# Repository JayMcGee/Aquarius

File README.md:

# Aquarius

The aquarius water quality evaluation station will be a programmable autonomous terminal. It will have acces to cellular network to transmit data to CloudIA, a scientific database and data visualisation interface.

The terminal evaluates water quality by acquiring acidity level (pH), water conductivity (µS/cm), dissolved oxygen (mg/L) and temperature(℃).  

-------------------------------------------------------------------------------------------------------------------------

La station d’évaluation de la qualité de l’eau Aquarius sera une borne autonome programmable. Elle aura la capacité de communiquer par réseau cellulaire ses données au logiciel CloudIA, une interface de visualisation de données scientifiques .

La borne permettra d’évaluer la qualité de l’eau en recueillant des mesures d’acidité (pH), de conductivité (µS/cm), de la concentration d’oxygène dissous (mg/L) et de la température (℃).

-------------------------------------------------------------------------------------------------------------------------

Aquarius is a Beaglebone Black with pH, dissolved oxygen, and conductivity sensors built by Atlas Scientific and a water temperature sensor by Dallas Semiconductor.

Each sensor has its own driver to calibrate or read a value. Those drivers are executed by an interface hosted on the apache server (/var/www) with a real-time interface written in Html connected to the server with Node.Js.

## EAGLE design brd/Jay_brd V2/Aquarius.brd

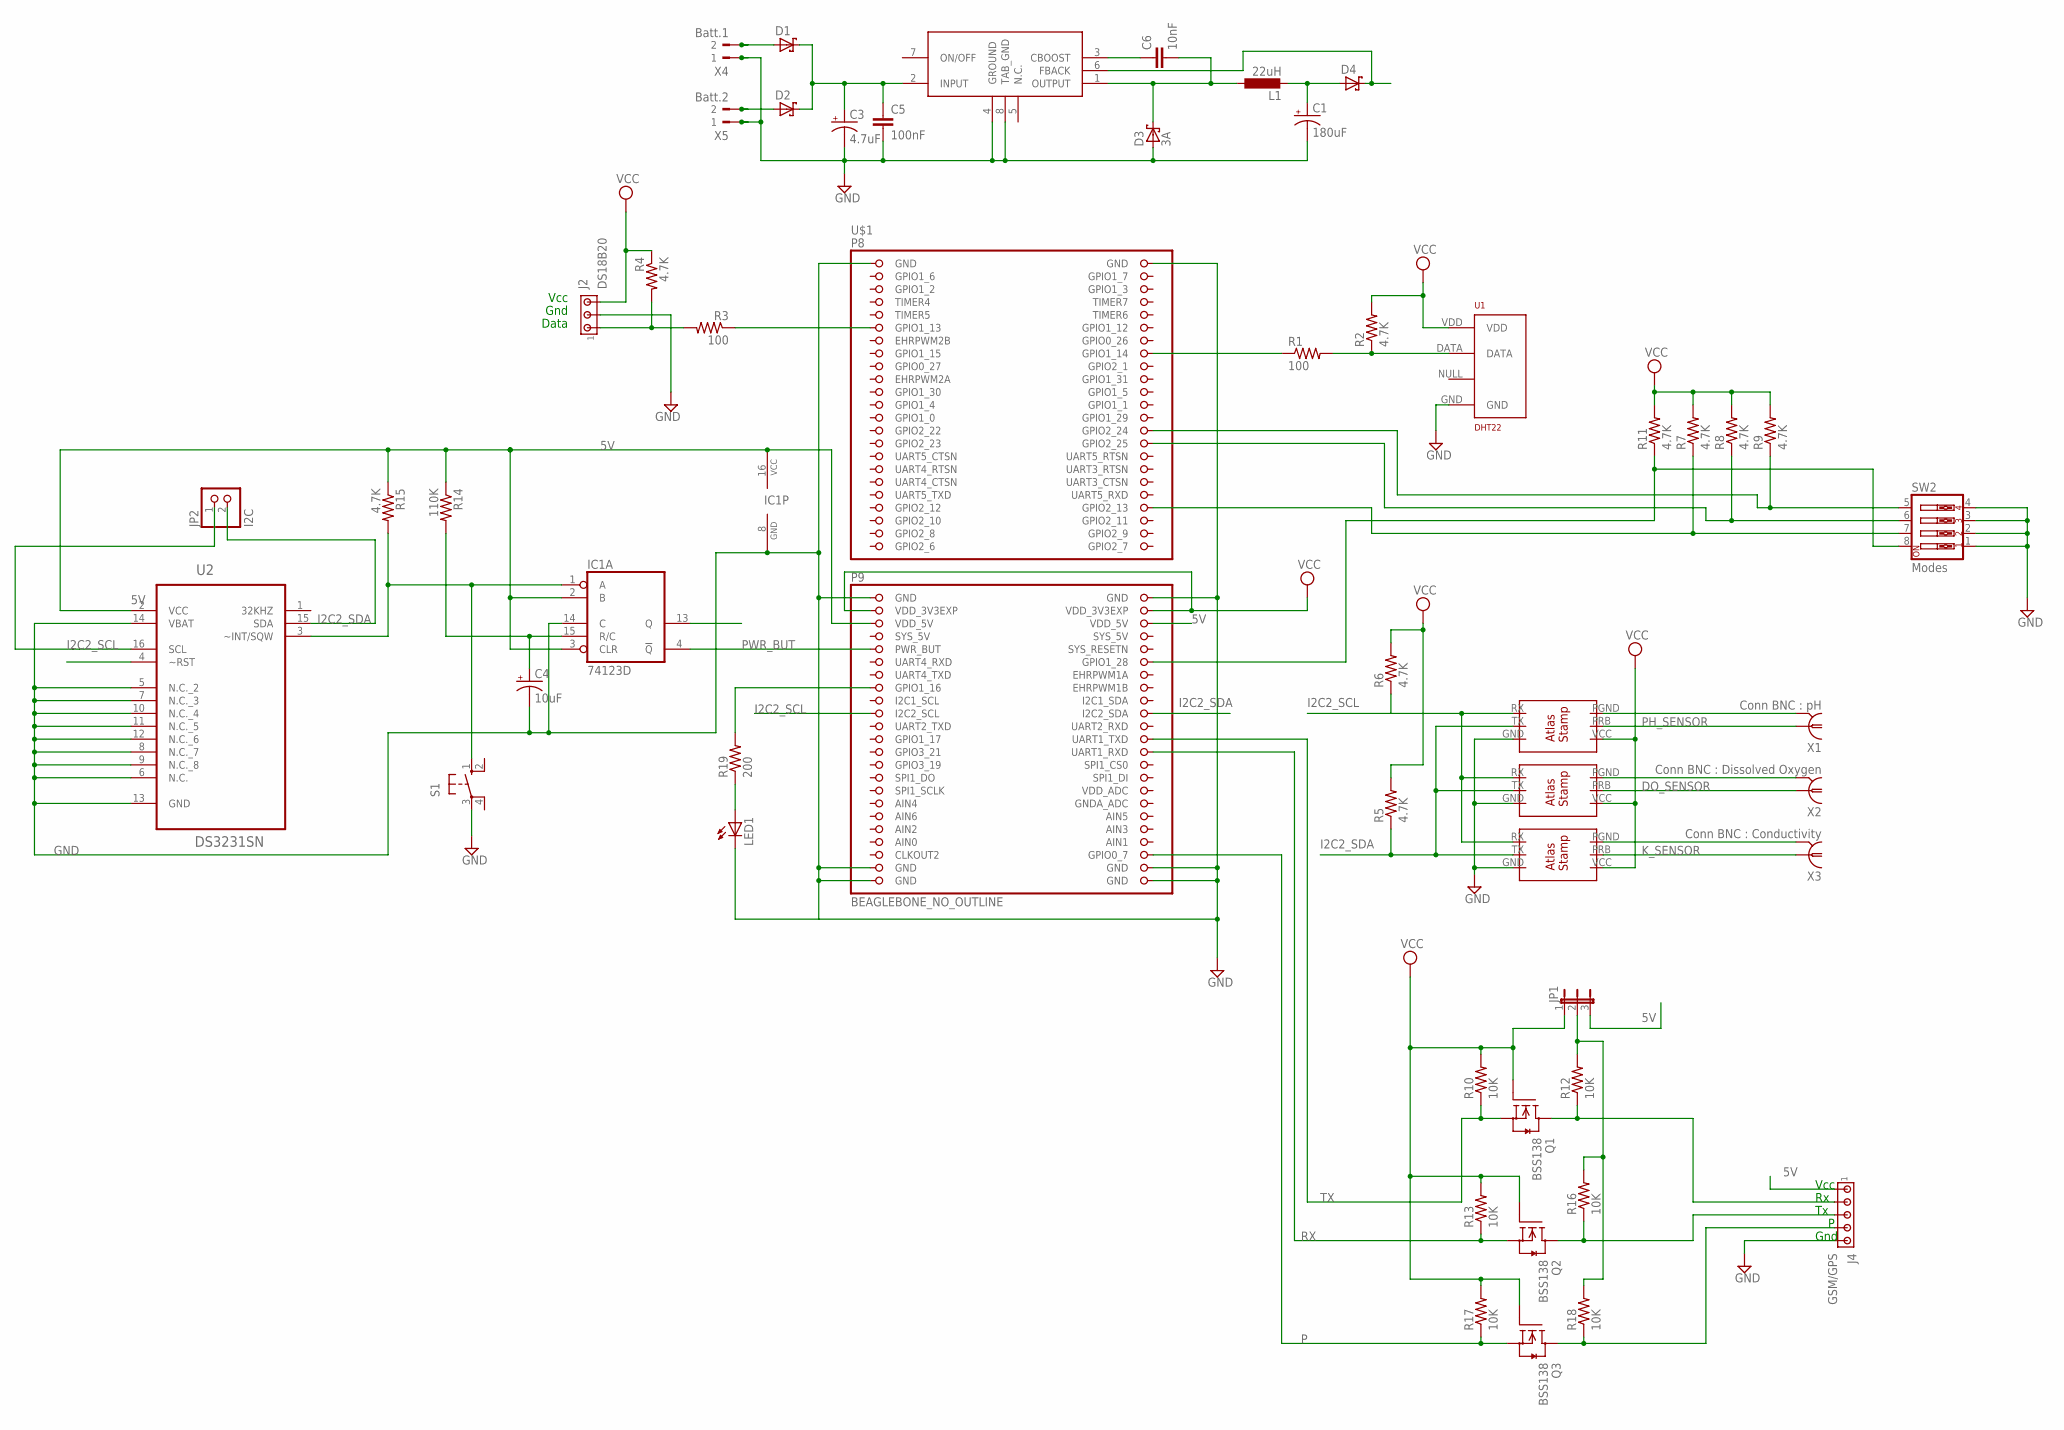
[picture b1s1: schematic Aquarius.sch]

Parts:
C1: 180uF; PANASONIC_D
C3: 4.7uF; PANASONIC_B
C4: 10uF; PANASONIC_B
C5: 100nF; C0805
C6: 10nF; C0805
D1, D2, D4: SCHOTTKY-DIODEDO201T15; DO201T15
D3: 3A; DO201T15
IC1: 74123D; SO16
J2: DS18B20; 10X03MTA
J4: GSM/GPS; 10X05MTA
JP1: JP2E; JP2
JP2: I2C; 1X02
L1: 22uH; EPCOS-10X10
LED1: LEDCHIP-LED0805; CHIP-LED0805
LM2678: LM2678KTW0007B; TO-PMOD7
Q1, Q2, Q3: BSS138; SOT23
R1, R3: 100; R0805
R2, R4, R5, R6, R7, R8, R9, R11, R15: 4.7K; R0805
R10, R12, R13, R16, R17, R18: 10K; R0805
R14: 110K; R0805
R19: 200; R0805
S1: 10-XX; B3F-10XX
SW2: Modes; EDG-04
U1: DHT22; AM2302
U2: DS3231SN; SOIC127P1032X265-16N
U$1: BEAGLEBONE_NO_OUTLINE; BEAGLEBONE_SHIELD_NO_OUTLINE
U$2, U$3, U$4: ATLAS_STAMP
X1: Conn BNC : pH; AMP_227161
X2: Conn BNC : Dissolved Oxygen; AMP_227161
X3: Conn BNC : Conductivity; AMP_227161
X4: Batt.1; 180G-2
X5: Batt.2; 180G-2

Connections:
5V: D4.C, IC1.2 (B), IC1.3 (CLR), IC1.16 (VCC), J4.1, JP1.3, LM2678.6 (FBACK), R14.1, R15.1, U2.2 (VCC), U$1.51 (VDD_5V), U$1.52 (VDD_5V)
AIN0: U$1.85 (AIN0)
DO_SENSOR: U$3.PRB, X2.1
GND: C1.-, C3.-, C4.-, C5.2, D3.A, IC1.8 (GND), IC1.14 (C), J2.2, J4.5, LED1.C, LM2678.4 (GROUND), LM2678.8 (TAB_GND), S1.3, SW2.1, SW2.2, SW2.3, SW2.4, U1.GND, U2.5 (N.C._2), U2.6 (N.C.), U2.7 (N.C._3), U2.8 (N.C._7), U2.9 (N.C._8), U2.10 (N.C._4), U2.11 (N.C._5), U2.12 (N.C._6), U2.13 (GND), U2.14 (VBAT), U$1.1 (GND), U$1.2 (GND), U$1.47 (GND), U$1.48 (GND), U$1.89 (GND), U$1.90 (GND), U$1.91 (GND), U$1.92 (GND), U$2.GND, U$3.GND, U$4.GND, X4.1, X5.1
I2C2_SCL: JP2.1, R6.1, U2.16 (SCL), U$1.65 (I2C2_SCL), U$2.RX, U$3.RX, U$4.RX
I2C2_SDA: JP2.2, R5.1, U2.15 (SDA), U$2.TX, U$3.TX, U$4.TX
INT: IC1.1 (A), R15.2, S1.1 (S), U2.3 (~INT/SQW)
K_SENSOR: U$4.PRB, X3.1
unnamed: J4.4, Q3.3 (D), R18.1
unnamed: D1.A, X4.2
unnamed: R1.2, R2.1, U1.DATA
unnamed: R3.1, U$1.11 (GPIO1_13)
unnamed: J2.1, R3.2, R4.2
unnamed: R1.1, U$1.16 (GPIO1_14)
unnamed: R7.1, SW2.7, U$1.40 (GPIO2_13)
unnamed: D2.A, X5.2
unnamed: C6.1, LM2678.3 (CBOOST)
unnamed: C3.+, C5.1, D1.C, D2.C, LM2678.2 (INPUT)
unnamed: U$2.PGND, X1.2
unnamed: C6.2, D3.C, L1.P$1 (1), LM2678.1 (OUTPUT)
unnamed: U$4.PGND, X3.2
unnamed: U$3.PGND, X2.2
unnamed: C1.+, D4.A, L1.P$2 (2)
unnamed: C4.+, IC1.15 (R/C), R14.2
unnamed: R11.1, SW2.8, U$1.58 (GPIO1_28)
unnamed: R8.1, SW2.6, U$1.30 (GPIO2_25)
unnamed: R9.1, SW2.5, U$1.28 (GPIO2_24)
unnamed: J4.3, Q2.3 (D), R16.1
unnamed: J4.2, Q1.3 (D), R12.1
unnamed: JP1.2, R12.2, R16.2, R18.2
unnamed: LED1.A, R19.1
unnamed: R19.2, U$1.61 (GPIO1_16)
P: Q3.2 (S), R17.1, U$1.88 (GPIO0_7)
PH_SENSOR: U$2.PRB, X1.1
PWR_BUT: IC1.4 (!Q), U$1.55 (PWR_BUT)
RX: Q2.2 (S), R13.1, U$1.72 (UART1_RXD)
SYS_5V: U$1.53 (SYS_5V)
TX: Q1.2 (S), R10.1, U$1.70 (UART1_TXD)
VCC: J2.3, JP1.1, Q1.1 (G), Q2.1 (G), Q3.1 (G), R2.2, R4.1, R5.2, R6.2, R7.2, R8.2, R9.2, R10.2, R11.2, R13.2, R17.2, U1.VDD, U$1.49 (VDD_3V3EXP), U$1.50 (VDD_3V3EXP), U$2.VCC, U$3.VCC, U$4.VCC

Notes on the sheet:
Vcc
Gnd
Data

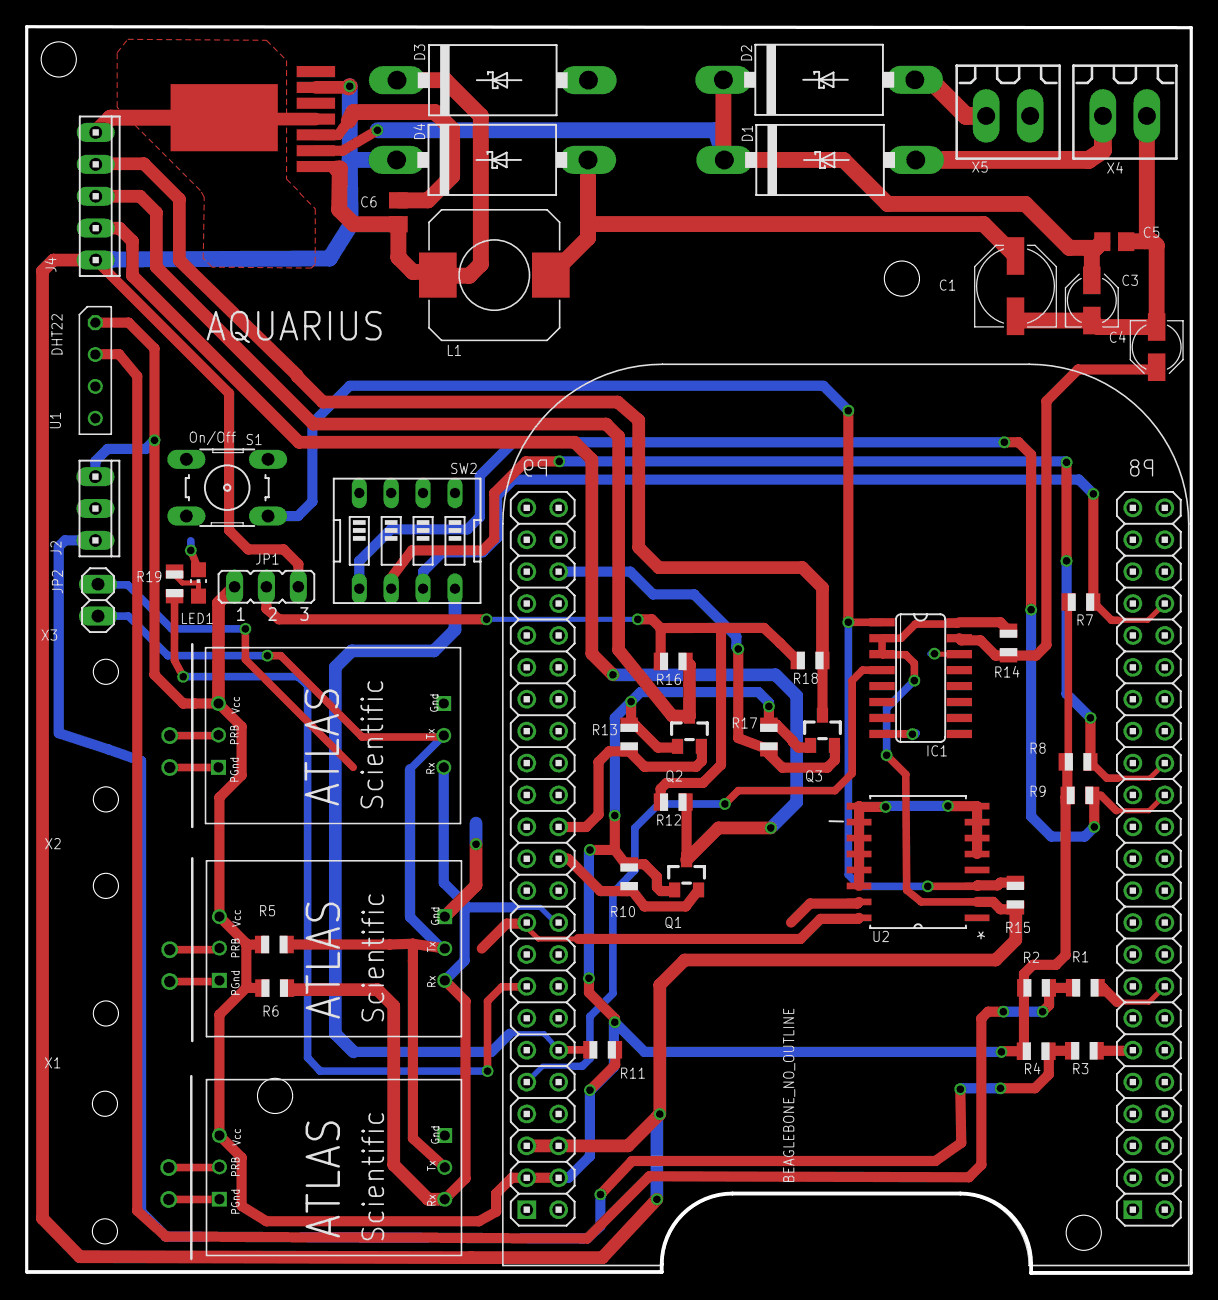
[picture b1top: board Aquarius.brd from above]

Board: 2 copper layers, 92.7 x 99.2 mm, 53 parts (1 on the bottom side), 37 nets.

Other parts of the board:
DRILEGEND: DRILEGEND

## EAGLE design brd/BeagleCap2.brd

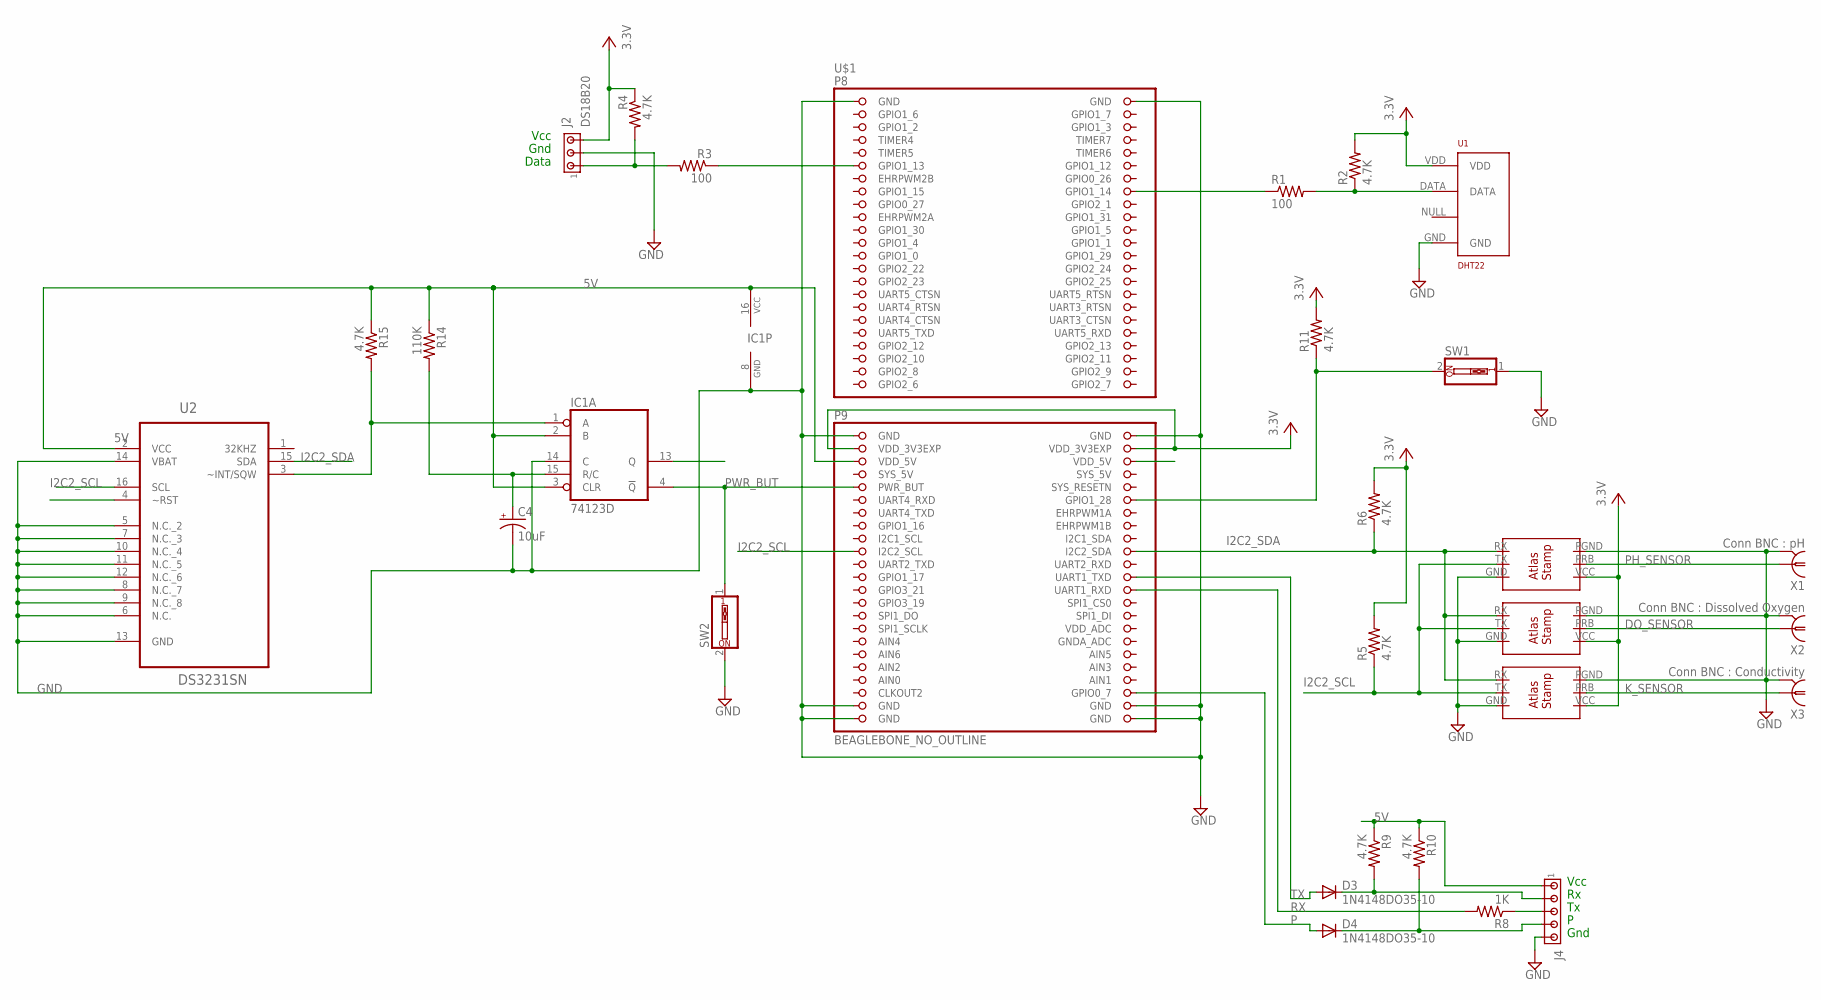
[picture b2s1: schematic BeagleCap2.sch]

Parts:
C4: 10uF; E2-5
D3, D4: 1N4148DO35-10; DO35-10
IC1: 74123D; SO16
J2: DS18B20; 10X03MTA
J4: MTA05-100; 10X05MTA
R1, R3: 100; R0805
R2, R4, R5, R6, R9, R10, R11, R15: 4.7K; R0805
R8: 1K; R0805
R14: 110K; R0805
SW1, SW2: SW_DIP-1; EDG-01
U1: DHT22; AM2302
U2: DS3231SN; SOIC127P1032X265-16N
U$1: BEAGLEBONE_NO_OUTLINE; BEAGLEBONE_SHIELD_NO_OUTLINE
U$2, U$3, U$4: ATLAS_STAMP
X1: Conn BNC : pH; AMP_227161
X2: Conn BNC : Dissolved Oxygen; AMP_227161
X3: Conn BNC : Conductivity; AMP_227161

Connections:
3.3V: J2.3, R2.2, R4.1, R5.2, R6.2, U1.VDD, U$1.49 (VDD_3V3EXP), U$1.50 (VDD_3V3EXP), U$2.VCC, U$3.VCC, U$4.VCC
5V: IC1.2 (B), IC1.3 (CLR), IC1.16 (VCC), J4.1, R9.1, R10.1, R14.1, R15.1, U2.2 (VCC), U$1.51 (VDD_5V)
AIN0: U$1.85 (AIN0)
DO_SENSOR: U$3.PRB, X2.1
GND: C4.-, IC1.8 (GND), IC1.14 (C), J2.2, J4.5, SW1.1, SW2.2, U1.GND, U2.5 (N.C._2), U2.6 (N.C.), U2.7 (N.C._3), U2.8 (N.C._7), U2.9 (N.C._8), U2.10 (N.C._4), U2.11 (N.C._5), U2.12 (N.C._6), U2.13 (GND), U2.14 (VBAT), U$1.1 (GND), U$1.2 (GND), U$1.47 (GND), U$1.48 (GND), U$1.89 (GND), U$1.90 (GND), U$1.91 (GND), U$1.92 (GND), U$2.GND, U$2.PGND, U$3.GND, U$3.PGND, U$4.GND, U$4.PGND, X1.2, X2.2, X3.2
I2C2_SCL: R5.1, U2.16 (SCL), U$1.65 (I2C2_SCL), U$2.TX, U$3.TX, U$4.TX
I2C2_SDA: R6.1, U2.15 (SDA), U$1.66 (I2C2_SDA), U$2.RX, U$3.RX, U$4.RX
INT: IC1.1 (A), R15.2, U2.3 (~INT/SQW)
K_SENSOR: U$4.PRB, X3.1
unnamed: R1.2, R2.1, U1.DATA
unnamed: R3.1, U$1.11 (GPIO1_13)
unnamed: J2.1, R3.2, R4.2
unnamed: R1.1, U$1.16 (GPIO1_14)
unnamed: R11.1, SW1.2, U$1.58 (GPIO1_28)
unnamed: D3.C, J4.2, R9.2
unnamed: J4.3, R8.1
unnamed: D4.C, J4.4, R10.2
unnamed: C4.+, IC1.15 (R/C), R14.2
P: D4.A, U$1.88 (GPIO0_7)
PH_SENSOR: U$2.PRB, X1.1
PWR_BUT: IC1.4 (!Q), SW2.1, U$1.55 (PWR_BUT)
RX: R8.2, U$1.72 (UART1_RXD)
SYS_5V: U$1.53 (SYS_5V)
TX: D3.A, U$1.70 (UART1_TXD)
VCC: R11.2

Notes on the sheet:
Vcc
Gnd
Data

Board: 2 copper layers, 29 parts (1 on the bottom side), 22 nets, no tracks yet.

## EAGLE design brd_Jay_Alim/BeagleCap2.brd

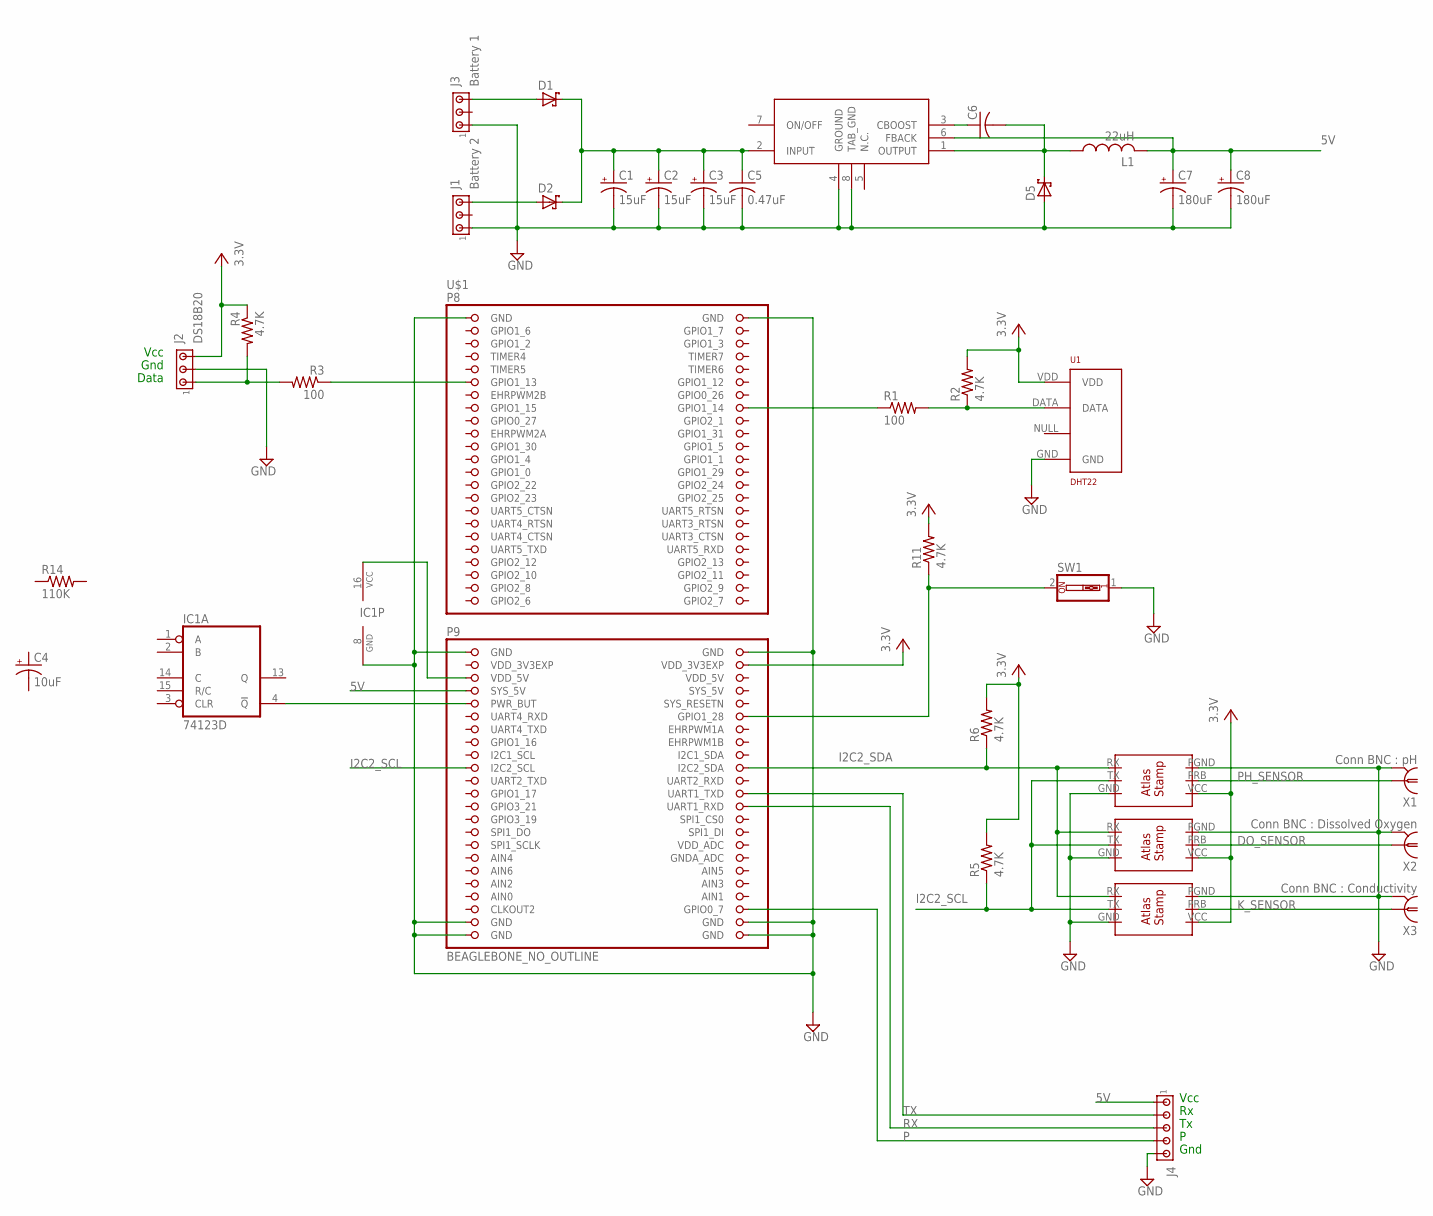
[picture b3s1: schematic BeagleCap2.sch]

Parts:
C1, C2, C3: 15uF; 153CLV-0405
C4: 10uF; E2-5
C5: 0.47uF; C025-025X050
C6: C-US025-025X050; C025-025X050
C7, C8: 180uF; E2,5-7
D1, D2: SCHOTTKY-DIODECB417-15; CB417-15
D5: SCHOTTKY-DIODEDO41-7; DO41-7
IC1: 74123D; SO16
J1: Battery 2; 10X03MTA
J2: DS18B20; 10X03MTA
J3: Battery 1; 10X03MTA
J4: MTA05-100; 10X05MTA
L1: 22uH; 0204/7
R1, R3: 100; R0805
R2, R4, R5, R6, R11: 4.7K; R0805
R14: 110K; R0805
SW1: SW_DIP-1; EDG-01
U1: DHT22; AM2302
U$1: BEAGLEBONE_NO_OUTLINE; BEAGLEBONE_SHIELD_NO_OUTLINE
U$2, U$3, U$4: ATLAS_STAMP
U$7: LM2678KTW0007B; TO-PMOD7
X1: Conn BNC : pH; AMP_227161
X2: Conn BNC : Dissolved Oxygen; AMP_227161
X3: Conn BNC : Conductivity; AMP_227161

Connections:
3.3V: J2.3, R2.2, R4.1, R5.2, R6.2, U1.VDD, U$1.50 (VDD_3V3EXP), U$2.VCC, U$3.VCC, U$4.VCC
5V: C7.+, C8.+, IC1.16 (VCC), J4.1, L1.2, U$1.51 (VDD_5V), U$1.53 (SYS_5V), U$7.6 (FBACK)
AIN0: U$1.85 (AIN0)
DO_SENSOR: U$3.PRB, X2.1
GND: C1.-, C2.-, C3.-, C5.2, C7.-, C8.-, D5.A, IC1.8 (GND), J1.1, J2.2, J3.1, J4.5, SW1.1, U1.GND, U$1.1 (GND), U$1.2 (GND), U$1.47 (GND), U$1.48 (GND), U$1.89 (GND), U$1.90 (GND), U$1.91 (GND), U$1.92 (GND), U$2.GND, U$2.PGND, U$3.GND, U$3.PGND, U$4.GND, U$4.PGND, U$7.4 (GROUND), U$7.8 (TAB_GND), X1.2, X2.2, X3.2
I2C2_SCL: R5.1, U$1.65 (I2C2_SCL), U$2.TX, U$3.TX, U$4.TX
I2C2_SDA: R6.1, U$1.66 (I2C2_SDA), U$2.RX, U$3.RX, U$4.RX
K_SENSOR: U$4.PRB, X3.1
unnamed: D2.A, J1.3
unnamed: D1.A, J3.3
unnamed: R1.2, R2.1, U1.DATA
unnamed: R3.1, U$1.11 (GPIO1_13)
unnamed: J2.1, R3.2, R4.2
unnamed: R1.1, U$1.16 (GPIO1_14)
unnamed: R11.1, SW1.2, U$1.58 (GPIO1_28)
unnamed: C1.+, C2.+, C3.+, C5.1, D1.C, D2.C, U$7.2 (INPUT)
unnamed: C6.1, U$7.3 (CBOOST)
unnamed: C6.2, D5.C, L1.1, U$7.1 (OUTPUT)
unnamed: IC1.4 (!Q), U$1.55 (PWR_BUT)
P: J4.4, U$1.88 (GPIO0_7)
PH_SENSOR: U$2.PRB, X1.1
RX: J4.3, U$1.72 (UART1_RXD)
TX: J4.2, U$1.70 (UART1_TXD)
VCC: R11.2
VDD_3V3EXP: U$1.49 (VDD_3V3EXP)
VDD_5V: U$1.52 (VDD_5V)

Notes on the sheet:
Vcc
Gnd
Data

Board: 2 copper layers, 35 parts (1 on the bottom side), 22 nets, no tracks yet.

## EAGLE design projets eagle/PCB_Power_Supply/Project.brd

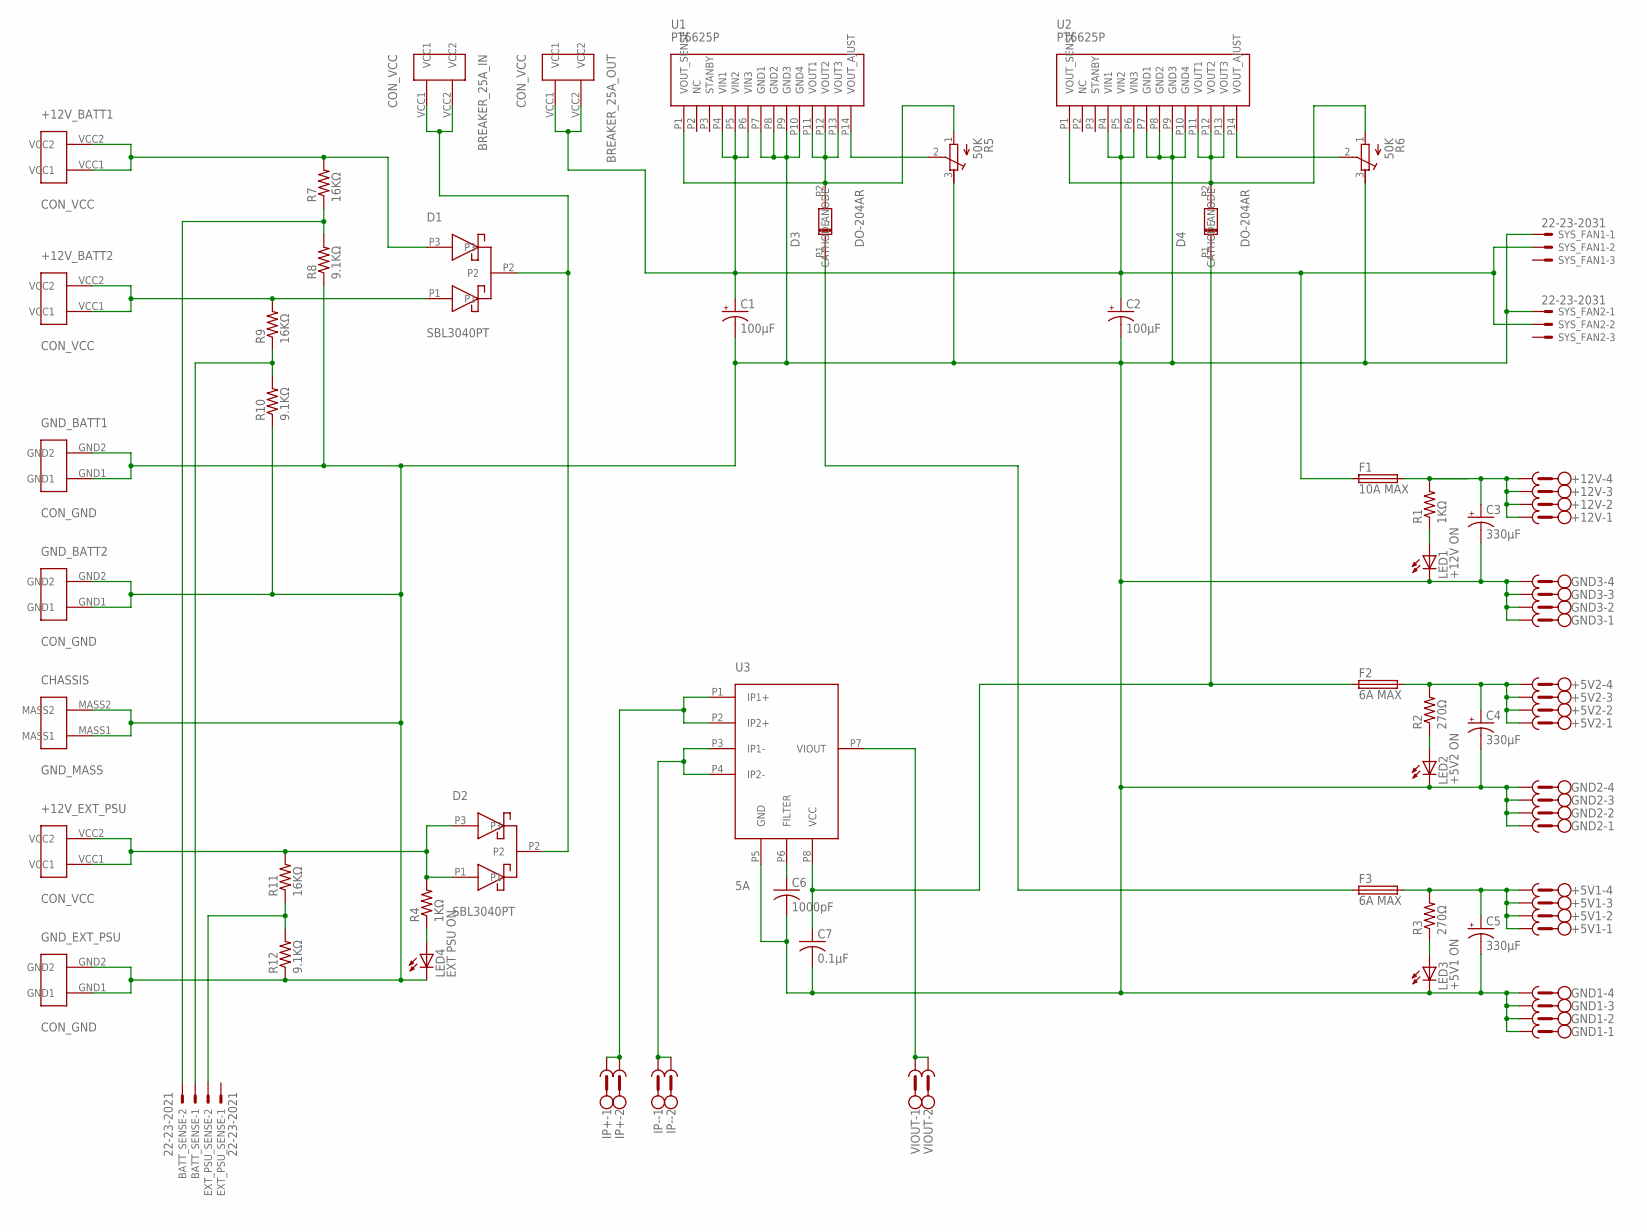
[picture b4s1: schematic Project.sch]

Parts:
+5V1, +5V2, +12V: MC1.5/4-G-3.81
+12V_BATT1, +12V_BATT2, +12V_EXT_PSU: CON_VCC
BATT_SENSE: 22-23-2021
BREAKER_25A_IN, BREAKER_25A_OUT: CON_VCC
C1, C2: 100µF; E2,5-6
C3, C4, C5: 330µF; E5-10,5
C6: 1000pF; C0805
C7: 0.1µF; C0805
CHASSIS: GND_MASS; CON_MASS
D1, D2: SBL3040PT
D3, D4: DO-204AR
EXT_PSU_SENSE: 22-23-2021
F1: 10A MAX; SH22,5
F2, F3: 6A MAX; SH22,5
GND1, GND2, GND3: MC1.5/4-G-3.81
GND_BATT1, GND_BATT2: CON_GND
GND_EXT_PSU: CON_GND
IP+: MC1.5/2-G-3.81
IP-: MC1.5/2-G-3.81
LED1: +12V ON; CHIP-LED0805
LED2: +5V2 ON; CHIP-LED0805
LED3: +5V1 ON; CHIP-LED0805
LED4: EXT PSU ON; CHIP-LED0805
R1, R4: 1KΩ; M0805
R2, R3: 270Ω; M0805
R5, R6: 50K; RTRIM3296Y
R7, R9, R11: 16KΩ; R0805
R8, R10, R12: 9.1KΩ; R0805
SYS_FAN1, SYS_FAN2: 22-23-2031
U1, U2: PT6625P
U3: 5A; ACS712
VIOUT: MC1.5/2-G-3.81

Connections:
GND: C1.-, C2.-, C3.-, C4.-, C5.-, C6.2, C7.2, CHASSIS.MASS1, CHASSIS.MASS2, GND1.1, GND1.2, GND1.3, GND1.4, GND2.1, GND2.2, GND2.3, GND2.4, GND3.1, GND3.2, GND3.3, GND3.4, GND_BATT1.GND1, GND_BATT1.GND2, GND_BATT2.GND1, GND_BATT2.GND2, GND_EXT_PSU.GND1, GND_EXT_PSU.GND2, LED1.C, LED2.C, LED3.C, LED4.C, R5.3 (A), R6.3 (A), R8.1, R10.1, R12.1, SYS_FAN1.1, SYS_FAN2.1, U1.P7 (GND1), U1.P8 (GND2), U1.P9 (GND3), U1.P10 (GND4), U2.P7 (GND1), U2.P8 (GND2), U2.P9 (GND3), U2.P10 (GND4), U3.P5 (GND)
unnamed: LED3.A, R3.1
unnamed: BATT_SENSE.2, R7.1, R8.2
unnamed: LED2.A, R2.1
unnamed: U3.P7 (VIOUT), VIOUT.1, VIOUT.2
unnamed: LED1.A, R1.1
unnamed: D4.P2 (CATHODE), R6.1 (E), U2.P1 (VOUT_SENSE), U2.P11 (VOUT1), U2.P12 (VOUT2), U2.P13 (VOUT3)
unnamed: +12V_BATT1.VCC1, +12V_BATT1.VCC2, D1.P3, R7.2
unnamed: +12V_BATT2.VCC1, +12V_BATT2.VCC2, D1.P1, R9.2
unnamed: +5V2.1, +5V2.2, +5V2.3, +5V2.4, C4.+, F2.2, R2.2
unnamed: BREAKER_25A_IN.VCC1, BREAKER_25A_IN.VCC2, D1.P2, D2.P2
unnamed: +12V.1, +12V.2, +12V.3, +12V.4, C3.+, F1.2, R1.2
unnamed: +12V_EXT_PSU.VCC1, +12V_EXT_PSU.VCC2, D2.P1, D2.P3, R4.2, R11.2
unnamed: +5V1.1, +5V1.2, +5V1.3, +5V1.4, C5.+, F3.2, R3.2
unnamed: LED4.A, R4.1
unnamed: IP-.1, IP-.2, U3.P3 (IP1-), U3.P4 (IP2-)
unnamed: R5.2 (S), U1.P14 (VOUT_AJUST)
unnamed: D3.P2 (CATHODE), R5.1 (E), U1.P1 (VOUT_SENSE), U1.P11 (VOUT1), U1.P12 (VOUT2), U1.P13 (VOUT3)
unnamed: R6.2 (S), U2.P14 (VOUT_AJUST)
unnamed: D3.P1 (ANODE), F3.1
unnamed: C6.1, U3.P6 (FILTER)
unnamed: BREAKER_25A_OUT.VCC1, BREAKER_25A_OUT.VCC2, C1.+, C2.+, F1.1, SYS_FAN1.2, SYS_FAN2.2, U1.P4 (VIN1), U1.P5 (VIN2), U1.P6 (VIN3), U2.P4 (VIN1), U2.P5 (VIN2), U2.P6 (VIN3)
unnamed: C7.1, D4.P1 (ANODE), F2.1, U3.P8 (VCC)
unnamed: IP+.1, IP+.2, U3.P1 (IP1+), U3.P2 (IP2+)
unnamed: BATT_SENSE.1, R9.1, R10.2
unnamed: EXT_PSU_SENSE.2, R11.1, R12.2

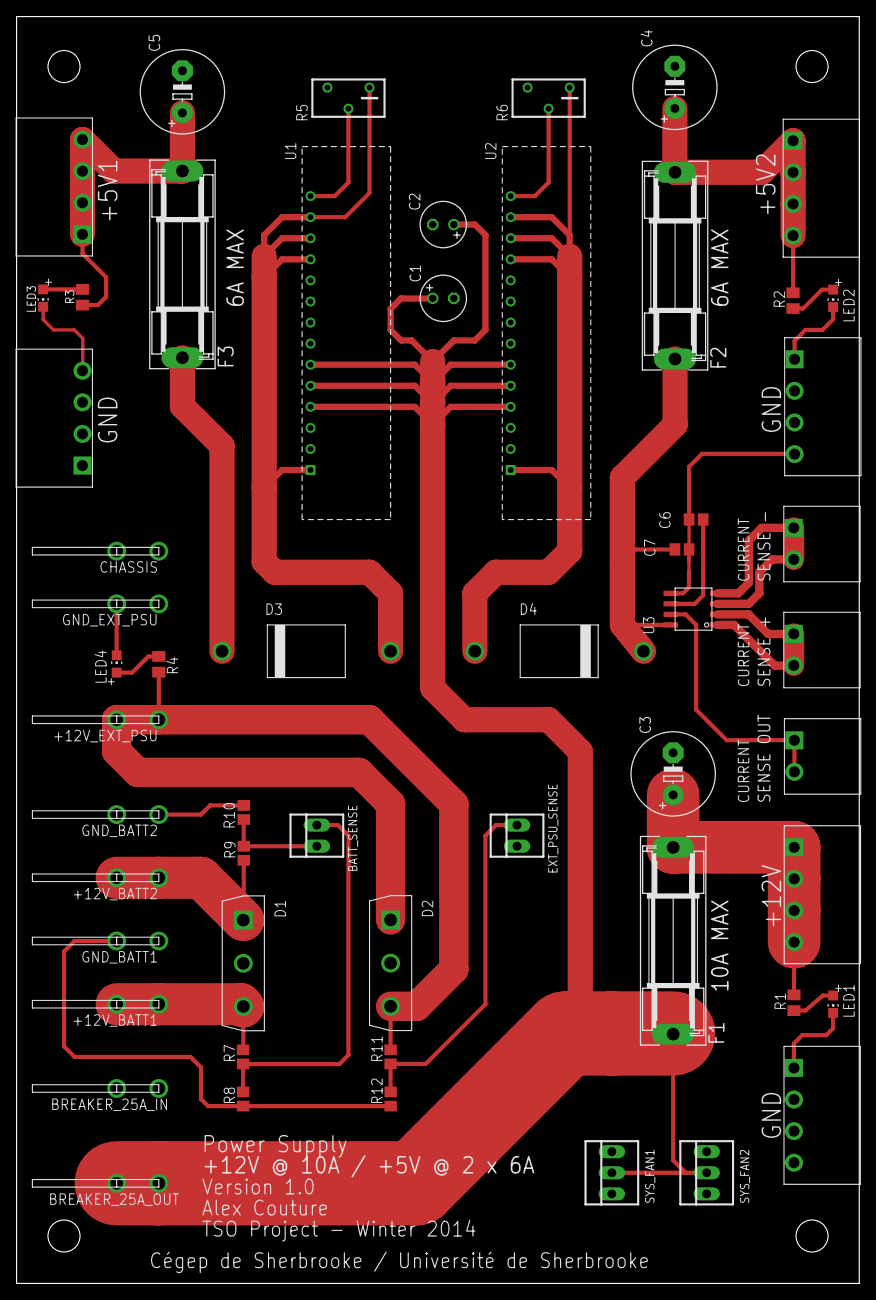
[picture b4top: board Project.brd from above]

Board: 2 copper layers, 101.6 x 152.7 mm, 55 parts (0 on the bottom side), 26 nets.

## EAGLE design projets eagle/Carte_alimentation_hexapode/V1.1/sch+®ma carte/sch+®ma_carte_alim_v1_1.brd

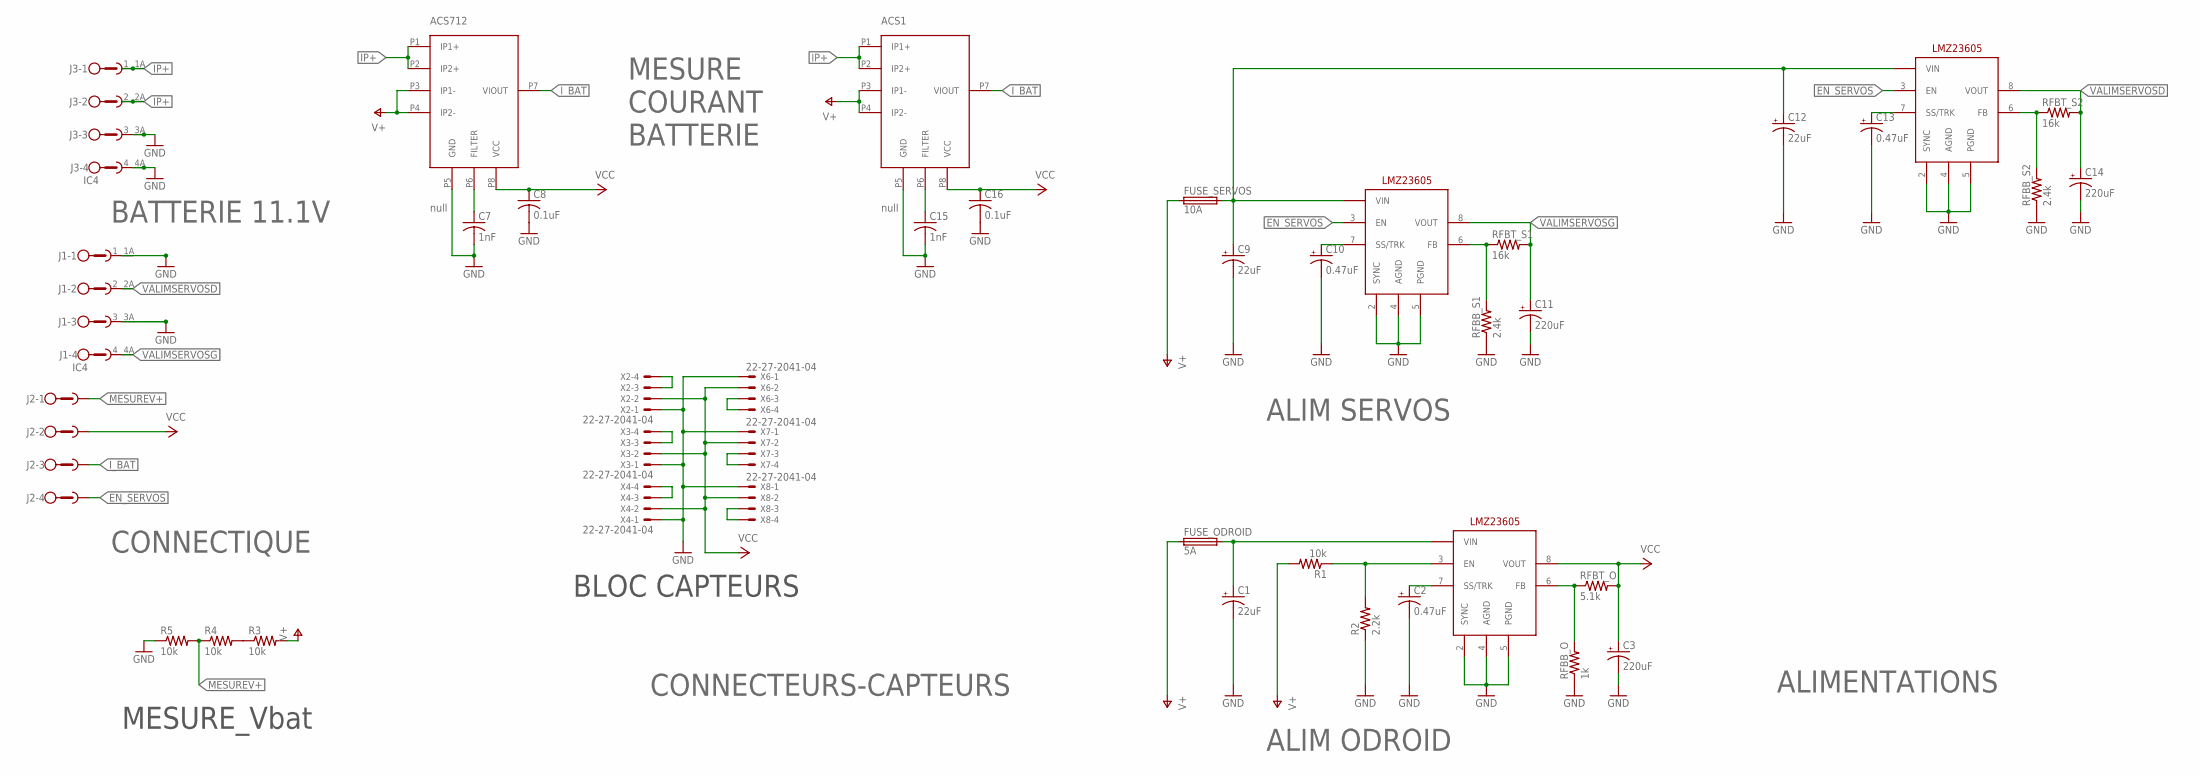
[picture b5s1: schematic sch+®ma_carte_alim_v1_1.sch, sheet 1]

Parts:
ACS1, ACS712: null; ACS712
ALIM_ODROID: LMZ23605
ALIM_SERVOS1, ALIM_SERVOS2: LMZ23605
C1, C9, C12: 22uF; E2,5-6
C2, C10, C13: 0.47uF; E2-5
C3, C11, C14: 220uF; E3,5-8
C7, C15: 1nF; C0805
C8, C16: 0.1uF; C0805
FUSE_ODROID: 5A; SH22,5
FUSE_SERVOS: 10A; SH22,5
J1, J3: IC4
J2: MC1.5/4-G-3.81
R1: 10k; R0805
R2: 2.2k; R0805
R3, R4, R5: 10k; M0805
RFBB_O: 1k; R0805
RFBB_S1, RFBB_S2: 2.4k; R0805
RFBT_O: 5.1k; R0805
RFBT_S1, RFBT_S2: 16k; R0805
X2, X3, X4, X6, X7, X8: 22-27-2041-04; 6410-04

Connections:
EN_SERVOS: ALIM_SERVOS1.3 (EN), ALIM_SERVOS2.3 (EN), J2.4
GND: ACS1.P5 (GND), ACS712.P5 (GND), ALIM_ODROID.2 (SYNC), ALIM_ODROID.4 (AGND), ALIM_ODROID.5 (PGND), ALIM_SERVOS1.2 (SYNC), ALIM_SERVOS1.4 (AGND), ALIM_SERVOS1.5 (PGND), ALIM_SERVOS2.2 (SYNC), ALIM_SERVOS2.4 (AGND), ALIM_SERVOS2.5 (PGND), C1.-, C2.-, C3.-, C7.2, C8.2, C9.-, C10.-, C11.-, C12.-, C13.-, C14.-, C15.2, C16.2, J1.1, J1.1A (2), J1.3 (1), J1.3A (2), J3.3 (1), J3.3A (2), J3.4 (1), J3.4A (2), R2.1, R5.1, RFBB_O.1, RFBB_S1.1, RFBB_S2.1, X2.1, X3.1, X4.1, X6.1, X7.1, X8.1
IP+: ACS1.P1 (IP1+), ACS1.P2 (IP2+), ACS712.P1 (IP1+), ACS712.P2 (IP2+), J3.1, J3.1A (2), J3.2 (1), J3.2A (2)
I_BAT: ACS1.P7 (VIOUT), ACS712.P7 (VIOUT), J2.3
MESUREV+: J2.1, R4.1, R5.2
unnamed: X6.3, X6.4
unnamed: ALIM_ODROID.7 (SS/TRK), C2.+
unnamed: ALIM_ODROID.6 (FB), RFBB_O.2, RFBT_O.1
unnamed: R3.1, R4.2
unnamed: ACS1.P6 (FILTER), C15.1
unnamed: X7.3, X7.4
unnamed: ALIM_ODROID.3 (EN), R1.1, R2.2
unnamed: X8.3, X8.4
unnamed: ACS712.P6 (FILTER), C7.1
unnamed: ALIM_SERVOS1.7 (SS/TRK), C10.+
unnamed: X2.3, X2.4
unnamed: X3.3, X3.4
unnamed: X4.3, X4.4
unnamed: ALIM_SERVOS1.6 (FB), RFBB_S1.2, RFBT_S1.1
unnamed: ALIM_SERVOS2.7 (SS/TRK), C13.+
unnamed: ALIM_SERVOS2.6 (FB), RFBB_S2.2, RFBT_S2.1
V+: ACS1.P3 (IP1-), ACS1.P4 (IP2-), ACS712.P3 (IP1-), ACS712.P4 (IP2-), FUSE_ODROID.1, FUSE_SERVOS.1, R1.2, R3.2
VALIMSERVOSD: ALIM_SERVOS2.8 (VOUT), C14.+, J1.2 (1), J1.2A (2), RFBT_S2.2
VALIMSERVOSG: ALIM_SERVOS1.8 (VOUT), C11.+, J1.4 (1), J1.4A (2), RFBT_S1.2
VCC: ACS1.P8 (VCC), ACS712.P8 (VCC), ALIM_ODROID.8 (VOUT), C3.+, C8.1, C16.1, J2.2, RFBT_O.2, X2.2, X3.2, X4.2, X6.2, X7.2, X8.2
VIN: ALIM_SERVOS1.1 (VIN), ALIM_SERVOS2.1 (VIN), C9.+, C12.+, FUSE_SERVOS.2
VINO: ALIM_ODROID.1 (VIN), C1.+, FUSE_ODROID.2

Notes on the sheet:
CONNECTIQUE
BATTERIE 11.1V
MESURE COURANT BATTERIE
MESURE_Vbat
BLOC CAPTEURS
ALIM ODROID
ALIM SERVOS
ALIMENTATIONS
CONNECTEURS-CAPTEURS

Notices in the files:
parts and their libraries:
m-pad-2.1: License : GNU General Public License version 2 (see bottom)
